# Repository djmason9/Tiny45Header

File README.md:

# Tiny45Header
a tinny header for arduino
Come see the article about how I did it here.
http://bitcows.com/?p=15

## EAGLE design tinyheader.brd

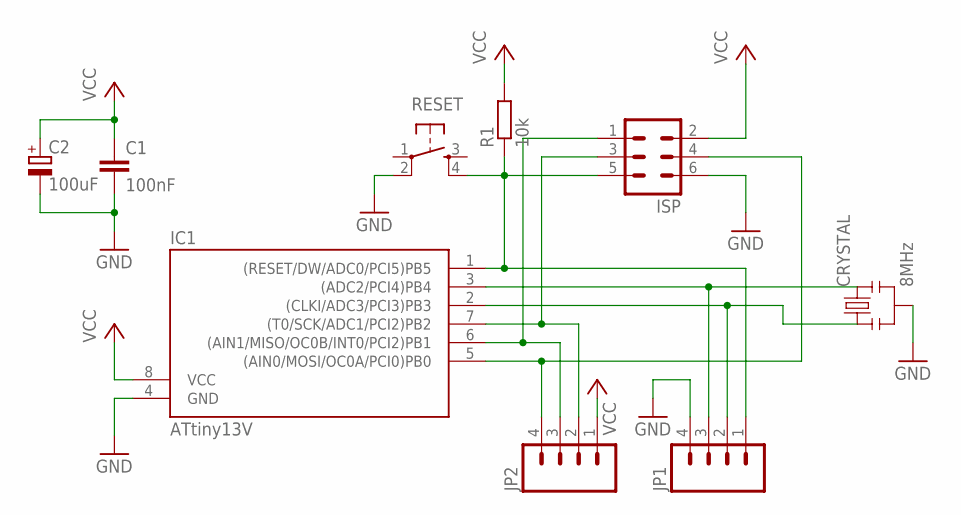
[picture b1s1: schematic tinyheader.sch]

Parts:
C1: 100nF; C025-025X050; MPN 1C20Z5U104M050B
C2: 100uF; E2,5-6E; MPN 100YXF100MEFC12.5X20
CRYSTAL: 8MHz; RESONATOR-PTH; MPN C8M000000L004
IC1: ATtiny13V; DIL08; MPN ATTINY13V-10PU
ISP: MA03-2
JP1, JP2: M04PTH; 1X04
R1: 10k; 0207/5V; MPN MCF 0.5W 10K
RESET: TAC_SWITCHSND; TACTILE_SWITCH_SMD

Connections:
GND: C1.2, C2.-, CRYSTAL.2, IC1.4 (GND), ISP.6, JP1.4, RESET.2
unnamed: CRYSTAL.1, IC1.2 ((CLKI/ADC3/PCI3)PB3), JP1.2
unnamed: IC1.1 ((RESET/DW/ADC0/PCI5)PB5), ISP.5, JP1.1, R1.1, RESET.4
unnamed: IC1.7 ((T0/SCK/ADC1/PCI2)PB2), ISP.3, JP2.2
unnamed: IC1.6 ((AIN1/MISO/OC0B/INT0/PCI2)PB1), ISP.1, JP2.3
unnamed: CRYSTAL.3, IC1.3 ((ADC2/PCI4)PB4), JP1.3
unnamed: IC1.5 ((AIN0/MOSI/OC0A/PCI0)PB0), ISP.4, JP2.4
VCC: C1.1, C2.+, IC1.8 (VCC), ISP.2, JP2.1, R1.2

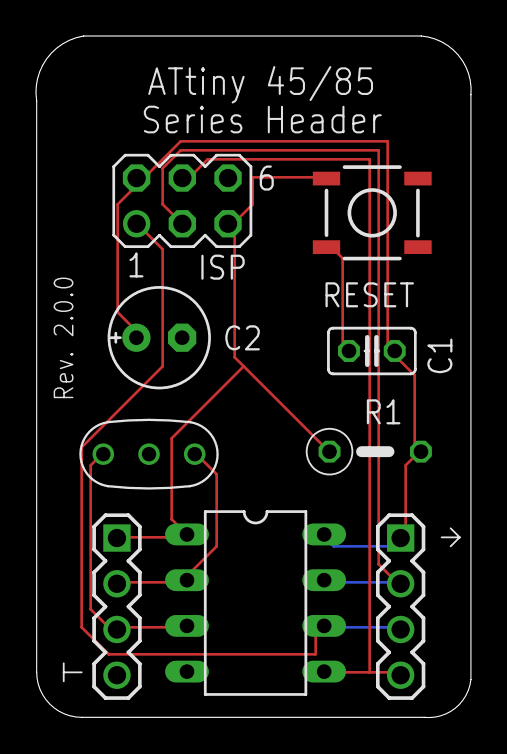
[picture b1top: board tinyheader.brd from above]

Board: 2 copper layers, 24.2 x 37.9 mm, 9 parts (0 on the bottom side), 8 nets.
